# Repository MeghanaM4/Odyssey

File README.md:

# Odyssey

> a project for [apex.hackclub.com](https://apex.hackclub.com) by Meghana Madiraju and help from Kieran Klukas

I have been in love with space for as long as I can remember, so when I heard Hack Club was letting teenagers send whatever they want 113,000 feet in the air I knew I had to do it. We get $100 per person to make an invention that'll go onto a high altitude balloon (HAB), and if you spend 30 hours on it you'll get to go to Boston for a hackathon where everyone will launch their payloads at the same time and make cool stuff.

## Quick Overview (what we're sending up)
- Sensor data from SMD components on PCB (stored on a microSD card)
- PCB powered by 3 AA batteries that can survive -45C
- Internal camera that can see internal content
- 8 digit 7-segment display that show the current altitude, which the int. camera can also see

## Collected data
- Pressure
- Magnetic field (3-axis)
- Internal temperature of payload
- Gyroscopic data (3-axis)

## Component Stack
| Component | Purpose |
| --------- | ------- |
| Seeed Studio XIAO RP2040 | Main microcontroller |
| MS560702BA03-50 | Altimeter |
| MPU-6050 | Gyroscope/accelerometer |
| ALS31313KLEATR-1000 | Magnetometer |
| Mini Body Cam | Internal view of payload |      

View the complete BOM [here](https://docs.google.com/spreadsheets/d/1y77u3fouo9j1fYMRJqijLE8DN1v_GkXtAQhd4oCJCtc/edit?usp=sharing)          
<br>
## PCB
             
<br>

## Timeline
| Phase | Status (%)|
| ------ | ------ |
| Research + Planning | 100% |
| Designing PCB and electronics layout | 100% | 
| Building payload | 100% |
| Coding firmware | 100% |
| Final tests and edits | 100% |
| Launch | 100% |

## Internal Camera View

## External View

## Design Process
My first sketch of Odyssey looked like this:
<br>

<br>
The main PCB (the green square artfully drawn in the center, complete with blue copper traces) with the XIAO and SMDs would process and collect data. The 4 digit 7-segment display displays the altitude of the payload (math that would be calculated from the barometer), and would sit in front of an internal camera (the purple box) so the altitude could be captured in the video feed. The internal camera would also look outside via the polycarbonate window that I am going to steal from my robotics team's shop (sorry Mr. S).      
The camera on top was originally meant to capture the sky, but then I found out all the payloads would be aligned on top of eachother candy-necklace style, so I scrapped that pretty quick.

The second sketch had some improvements:
<br>

<br>

I thought that we would need 3 PCBs: one for the main sensors, one for the LCD screen and 7-seg display, and one for the pyranometer. What's overkill? This obviously was taken out after I thought about a bit more (see: overkill) and after I saw the customs and duties taxes. The yellow stuff you see on the walls is my artistic interpretation of spray insulation.      

I really wanted our data to be space-focused, so getting a pyranometer to measure cosmic ray data was at the top of my list. Unfortunately, the Apogee Instrument component I found was a massive pain to work with, so I decided to just scrap it. If I get the basic functionality of everything else working, then I'll look into aurora borealis or radiation detection. The challenge is that those have to be on the outside of the payload, or at least shielded solely by polycarb or some other low-z window material.

I also drew a sketch of what I wanted the internal view to be:
<br>

<br>

Here's an updated internal view with a smaller box and an updated layout:
<br>

<br>

At this point, I planned for a PCB to store data from 3 sensors onto a microSD card, an internal camera that I charged to take a video of the entire flight, and 2 4-digit 7-segment displays to show the altitude as the payload rose. I hadn't yet figured out how to power the 7seg displays, or how I was going to control it (since the PCB didn't have enough open GPIO pins). I ordered 2 PCBAs of JLCPCB (I had to ship it to my friend in Canada, who then shipped it to me, to avoid the tariffs), Kieran and I soldered  the XIAO RP2040 on the back, and we started reading from the sensors.      
<br>

<br>
I wanted the current altitude of the payload displayed on two 4-digit 7-segment displays so that the internal camera could see it, and realized quickly that I would need like 28 GPIO pins if I directly connected them both to a microcontroller, so that was a no go. I then found out that there's ICs that are made for controlling these kinds of things, so I spent the last of my $100 grant and got to work.

Bit of a change in plans. The MAX7219 driver chip I wanted to use to control the 7 segment displays didn't work and the libraries people used were like falling apart, so I was on the verge of severely rethinking plans. Then, Kieran came up with the wonderful idea of transmitting the altimeter data from the XIAO RP2040 (on the main PCB) to another microcontroller, so that we would have enough GPIO pins to directly wire the 7seg display.

Then, we remembered that we need two 4 digit 7seg displays, so we were like "let's send data from the xiao rp2040 to 2 other microcontrollers, one has the first 4 digits of the altitude and one has the last 4." Insane. So I'm working on that right now. We got connection between the xiao rp2040 and a xiao nrf52840 sense, but the sense doesn't have enough GPIO pins so Kieran kindly decided to lend me 2 orpheus picos (shout out Adam).
> An Orpheus Pico is a cheaper version of the raspberry pi pico made by @adammakesthingsdev that Hack Club used to make and distribute to people

I keep getting a transmission timing error between the xiao rp2040 and the pico, and I don't know how to fix it. Part of me thinks it's how I wired my pull up resistors (translating breadboard wiring to parallel and series diagrams in my head is rough), but I have no idea. At least I can flash code on the pico now, I dealt with a BOOTSEL issue for like 3 hours yesterday.

So after days of trying to get I2C to work, I decided to switch to SPI. And I kept getting errors there too. I think I've discovered my problem: because I'm using an orpheus pico but setting Arduino IDE's board to a raspberry pi pico, the default MOSI, MISO, and SCK (and therefore the SCL and SDA) pins don't match the orpheus pico's (because they have different internal stuff). So the problem was arduino the whole time. I knew that was gonna be an issue. Damn it. When I tried to set the SDA and SCL pins before Wire.begin() the pico used to crash and not execute any code, that's why I switched to SPI. this is crazy.

So, I'm spending more money. I've given up on communicating between the xiao rp2040 and another microcontroller. I'm going to buy an 8 digit 7seg display that has 5 pins that I can directly wire to my xiao rp2040. My only concern is that it uses the same MAX7219 driver chip that didn't work for me before (and whose library was also garbage), but other people got this thing to work and maybe those errors was me wiring wrong or doing something dumb. I've been trying for like a week to get this right and now I have to just pray to god that this New Method will work. This sucks balls.

The new display came, and after it (inevitably) didn't work, I resoldered the connections I had. Who knew that when your wires look like this some stuff is bound to break?

Anyway, here's what it looked like after. 

> I made the mistake of getting 16 gauge wire. I spent ages at Lowe's trying to find like reasonable electrical wire but all of it was like Lamp Wire or Speaker Wire or Roof Tubing Heavy Duty Fracking Wire. Then, I tried to look for 24 gauge wire (thanks @Karmanyaah) but apparently none exists within a 50 mile radius of me so I had to buy it from amazon and get it shipped the next day. What you see above is me thinning out the ends of the wire so I can actually solder it. I've added an "idiot" column to my BOM.            

The display worked! Wow, the wonders of not being lazy.

But that was on the wrong microcontroller. I'd gotten it to work on the XIAO nRF52840 Sense that I had because, for some reason, it wouldn't work on my xiao RP2040. I dug out my dad's multimeter and found out it wasn't because of my soldering (win), but because of STUPID PIN ASSIGNMENTS. WHAT THE FREAK. On the xiao nRF you just put the GPIO assignment (D7 = 7), which is fine. But on the xiao rp2040 for some reason D10 is actually 3??? What?? Anyway, I got it work.

So with my camera set up (I had to buy another one since the first one was too cheap to work), the inside of the payload will look a bit like this. (the camera quality is better than this, I'm using a screenshot from a video of a video)

I've weighed the thing and I'm about 100g over (the whole thing is supposed to be 3/4 lbs or ~340 grams), so I'm planning to build the entire thing, be as wire-conscious as possible, and use my soldering iron to burn away any excess weight I might have after it's all done.
> Fun Fact: Burnt stryofoam fumes are carcinogenic!

I'm glad I'm not like insanely overweight because I hadn't weighed it up till now and was just kind of praying.

Yeah okay it's overweight. I didn't realize how much 100g of styrofoam actually was. It's like, a lot. I spent 10 minutes using my crappy $10 soldering iron to burn/melt away some of the sides of the box, and then I just started coughing a ton so I was like "that's probably a sign to stop" 

> did I mention styrofoam fumes are carcinogenic?

Anyway, I only got a gram off or something. 

Then, as I waited for my bedroom to stop becoming a Hazardous Zone, I went outside and started chopping away at the box with a massive serated kitchen knife. That only yielded about a gram, too. No dice.
> My window was open and the ceiling fan was running. My lungs feel okay.

Then I was just like "screw it" and destroyed my box to make a smaller one. An hour later, ta da! All that funky texture is my previous attempt at burning away material, and (as I'm sure you can guess) ruining my soldering iron in the process. It's strong, it'll push through.

Updated inside view (no wires): 

Tomorrow I'll glue the sides of the box together with gorilla glue and spray insulation/gap filler, and then I'll start soldering. We're so back.
> It's 2am.

So I sprayed insulation and gap filler and got everything pretty nice and laid out. I soldered the entire circuit and with some minor adjustments (I soldered the wrong pins of the rocker switch and I switched the 5V and GND junctions), it worked. My 7 segment display is showing altitude and everything is awesome.

So then I stuck all its guts inside, taped some stuf down, and it now looks like this. Everything is awesome.

So remember when I said everything is awesome? Turns out it's not. I'd run code for the 7 segment display and that worked, and I had code to log sensor data onto the microSD card, so I assumed everything would be fine when you put them together. Well was it? No, of course not. I was using SPI communication for both storing data on the microSD card and communicating with the 7 segment display. When I implemented the LedControl library in my log code, my display worked but it kept printed "Error opening file" to the serial monitor.

_Frick_ 

The display and SD card trying to communicate at the same time was screwing everything up, because signals it was sending overlapped with eachother and caused a bunch of nonsense. I immediately assumed that the problem couldn't be fixed, and that I'd have to sacrifice the display and it would all be sad. I'd tried to manually activate and deactivate the display by digitalWriting its chip select LOW and HIGH whenever the display was supposed to be silent, but it didn't work.
> Apparently, you're not supposed to do that.

Then, I thought that I should only update the display once every second, hoping that would slow down communication and the handling would be better. Also didn't work.

_Friiiiiiick_

Then, it hit me. I used the xiao's MISO pin for both components, not thinking about how that literally makes no sense. My serial clock was also connected to a pin that was already in use by the PCB, so that was an issue as well. I had 2 unconnected pins on my PCB. One I was using as my display's chip select (by complete chance) and one that I hadn't soldered to anything. I needed 3. DIN, CLK, and CS. I looked back at my KiCAD schematic and saw that I had interrupt pins for my magnetometer and my gyroscope, and realized I wasn't using them at all. 
> I was using polling, which is apparently way less efficient.

Since I wasn't using either of those pins, I soldered my DIN wire to my magnetometer interrupt pin and my CLK to the other unconnected GPIO I had. Still didn't work.

_Friiiiiiiiiiiiiiiiiiiiiiick_

Then I was like "what if the magnetometer is still using the interrupt pin, even though I'm not. It could be sending whatever it wants, or like bugging out and being random" (technical terms). So I cut its little ssop 8 legs off and tested it. 

It worked.

> Thank god, I was nearing the martian levels of self-inflicted disasters

Anyway, so everything's good now. Look at the inside!

I'm not doing a polycarb window anymore, partly because of time (my flight's tomorrow) and partly cause I'm scared to do anything else to this thing. I'm pretty happy with it.

----------------------
Update: I launched! Apex was an awesome event. After a nasty takeoff that made everyone's payloads hit the ground on takeoff, the balloons rose to about 100,000 feet in the air before popping. Unfortunately, the balloon my payload was on (there were 2) was the one that got stuck in a tree and was unrecoverable. So although I will never get to see what the camera saw, I can't believe I actually did it.

_This update was made about 4 months after Apex happened. I got a bit sidetracked (check out [Pathfinder](https://pathfinder.hackclub.com) and [Daydream](https://daydream.hackclub.com))_

## Big thank you to
-My teachers for putting up with my late work      
-My parents for letting me work on this instead of school       
-Kieran for answering all my questions

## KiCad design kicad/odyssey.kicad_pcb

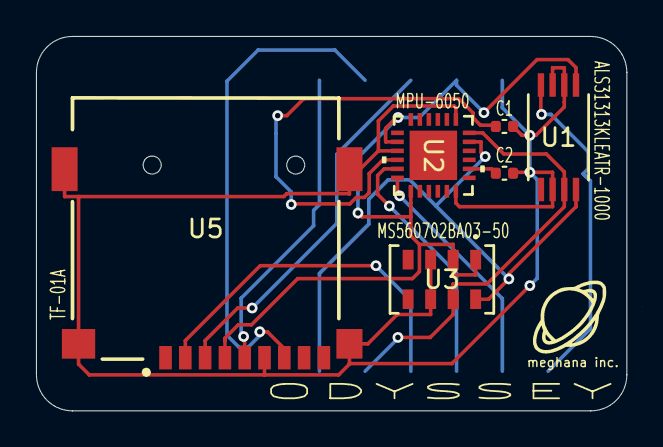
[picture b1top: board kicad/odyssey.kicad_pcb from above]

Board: 2 copper layers, 32.8 x 20.8 mm, 7 parts (1 on the bottom side), 13 nets.

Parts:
C1, C2: C; C_0402_1005Metric
U1: ALS31313KLEATR-1000; TSSOP8_LE_ALM
U2: MPU-6050; QFN24_4X4X0P9-0P5_TDK
U3: MS560702BA03-50; SON8_MS5611_TEC
U4: XIAO-RP2040-SMD
U5: TF-01A

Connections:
3.3V: U1.1 (VCC), U2.8 (VLOGIC), U2.13 (VDD), U3.1 (VDD), U3.2 (PS), U4.12 (3V3), U5.4 (VDD)
GND: C1.1, C2.1, U1.2 (ADR0), U1.3 (GND), U1.6 (ADR1), U2.1 (CLKIN), U2.9 (AD0), U2.18 (GND), U3.3 (GND), U3.6 (SDO), U4.13 (GND), U5.6 (VSS), U5.MP1 (SHIELD), U5.MP2 (SHIELD), U5.MP3 (SHIELD), U5.MP4 (SHIELD)
GYROFSYNC: U2.11 (FSYNC), U4.3 (GPIO28_A2_D2)
GYROINT: U2.12 (INT), U4.2 (GPIO27_A1_D1)
MAGINT: U1.4 (*INT), U4.1 (GPIO26_A0_D0)
MSDCD: U4.4 (GPIO29_A3_D3), U5.2 (CD/DAT3)
MSDCLK: U4.9 (GPIO2_D8_SCK), U5.5 (CLK)
MSDMISO: U4.10 (GPIO4_D9_MISO), U5.7 (DAT0)
MSDMOSI: U4.11 (GPIO3_D10_MOSI), U5.3 (CMD)
unnamed: C2.2, U2.20 (CPOUT)
unnamed: C1.2, U2.10 (REGOUT)
SCL: U1.8 (SCL), U2.23 (SCL), U3.8 (SCLK), U4.6 (GPIO7_D5_SCL)
SDA: U1.7 (SDA), U2.24 (SDA), U3.7 (SDI/SDA), U4.5 (GPIO6_D4_SDA)

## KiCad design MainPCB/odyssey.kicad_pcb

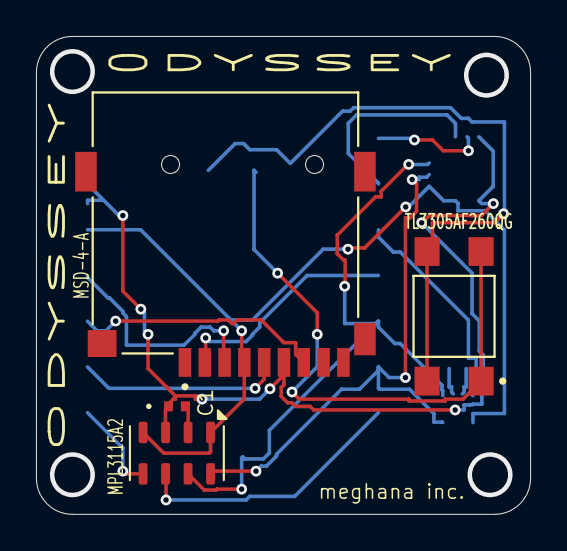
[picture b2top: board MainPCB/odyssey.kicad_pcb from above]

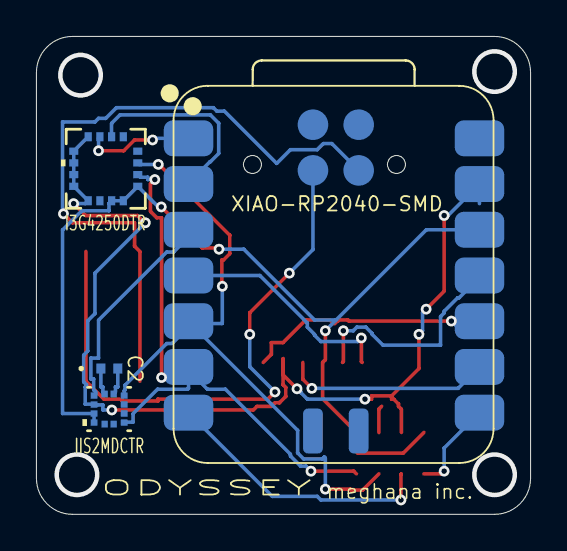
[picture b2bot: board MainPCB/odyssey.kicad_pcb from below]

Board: 2 copper layers, 27.5 x 26.5 mm, 8 parts (4 on the bottom side), 18 nets.

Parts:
C1: 0402B104K160CT; CAP_0402_N_WAL
C3: C2; CAP_0402_N_WAL
J1: MSD-4-A; CUI_MSD-4-A
U1: I3G4250DTR
U2: IIS2MDCTR
U3: XIAO-RP2040-SMD
U4: TL3305AF260QG; SW_TL3305AF260QG
U5: MPL3115A2; NXP_LGA-8_3x5mm_P1.25mm_H1.1mm

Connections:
3.3V XIAO: J1.4 (VDD), U1.1 (VDD_IO), U1.15 (RES), U1.16 (VDD), U2.9 (VDD), U2.10 (VDD_IO), U3.12 (3V3), U5.1 (VDD), U5.4 (VDDIO)
CLK: J1.5 (CLK), U3.9 (GPIO2_D8_SCK)
GND: C1.1, J1.6 (VSS), U1.8 (RES), U1.9 (RES), U1.10 (RES), U1.11 (RES), U1.12 (RES), U1.13 (GND), U2.8 (GND), U3.13 (GND), U5.3 (GND)
I3G4 INT1: U1.7 (INT1), U3.1 (GPIO26_A0_D0)
I3G4 INT2: U1.6 (DRDY/INT2), U3.2 (GPIO27_A1_D1)
IIS2 INT: U2.7 (INT/DRDY), U3.3 (GPIO28_A2_D2)
MISO: J1.7 (DAT0), U3.10 (GPIO4_D9_MISO)
MOSI: J1.3 (CMD), U3.11 (GPIO3_D10_MOSI)
MPL INT1: U3.7 (GPIO0_D6_TX), U5.6 (INT1)
MPL INT2: U3.8 (GPIO1_D7_CSn_RX), U5.5 (INT2)
MSD STAT: J1.2 (CD/DAT3), U3.4 (GPIO29_A3_D3)
unnamed: C3.1, U2.6 (GND)
unnamed: C3.2, U2.5 (C1)
unnamed: U3.20 (GND), U4.3, U4.4
unnamed: U3.19 (RST), U4.1, U4.2
unnamed: C1.2, U5.2 (CAP)
XIAO SCL: U1.2 (SCL/SPC), U2.1 (SCL/SPC), U3.6 (GPIO7_D5_SCL), U5.8 (SCL)
XIAO SDA: U1.3 (SDA/SDI/SDO), U2.4 (SDA/SDI/SDO), U3.5 (GPIO6_D4_SDA), U5.7 (SDL)

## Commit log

2025-04-26 main pcb upload and pcb folders
2025-04-27 updating main pcb
2025-04-27 docs: update readme
2025-04-27 chore: move to standard kicad layout
2025-04-27 feat: update license to mit
2025-04-27 feat: shrink board and autoroute
2025-04-27 feat: add production options
2025-04-29 updating pcb
2025-05-10 trying firmware stuff
2025-05-10 adding images
2025-05-12 PCB picture
2025-05-12 pcb image
2025-05-16 imgs update
2025-05-16 imgs
2025-05-19 test complete
2025-05-19 counter
2025-06-03 primitive sensor reading tests
2025-06-03 fix image
2025-06-03 plotting and logging sensor data !!
2025-06-12 auauauau
2025-06-16 losing my mind
2025-06-17 cleaning up firmware + update readme
2025-06-19 updating firmware + img
2025-10-25 Modify camera description in README
    Updated README to reflect changes in camera description.
2025-10-25 Final update (4 months late)
